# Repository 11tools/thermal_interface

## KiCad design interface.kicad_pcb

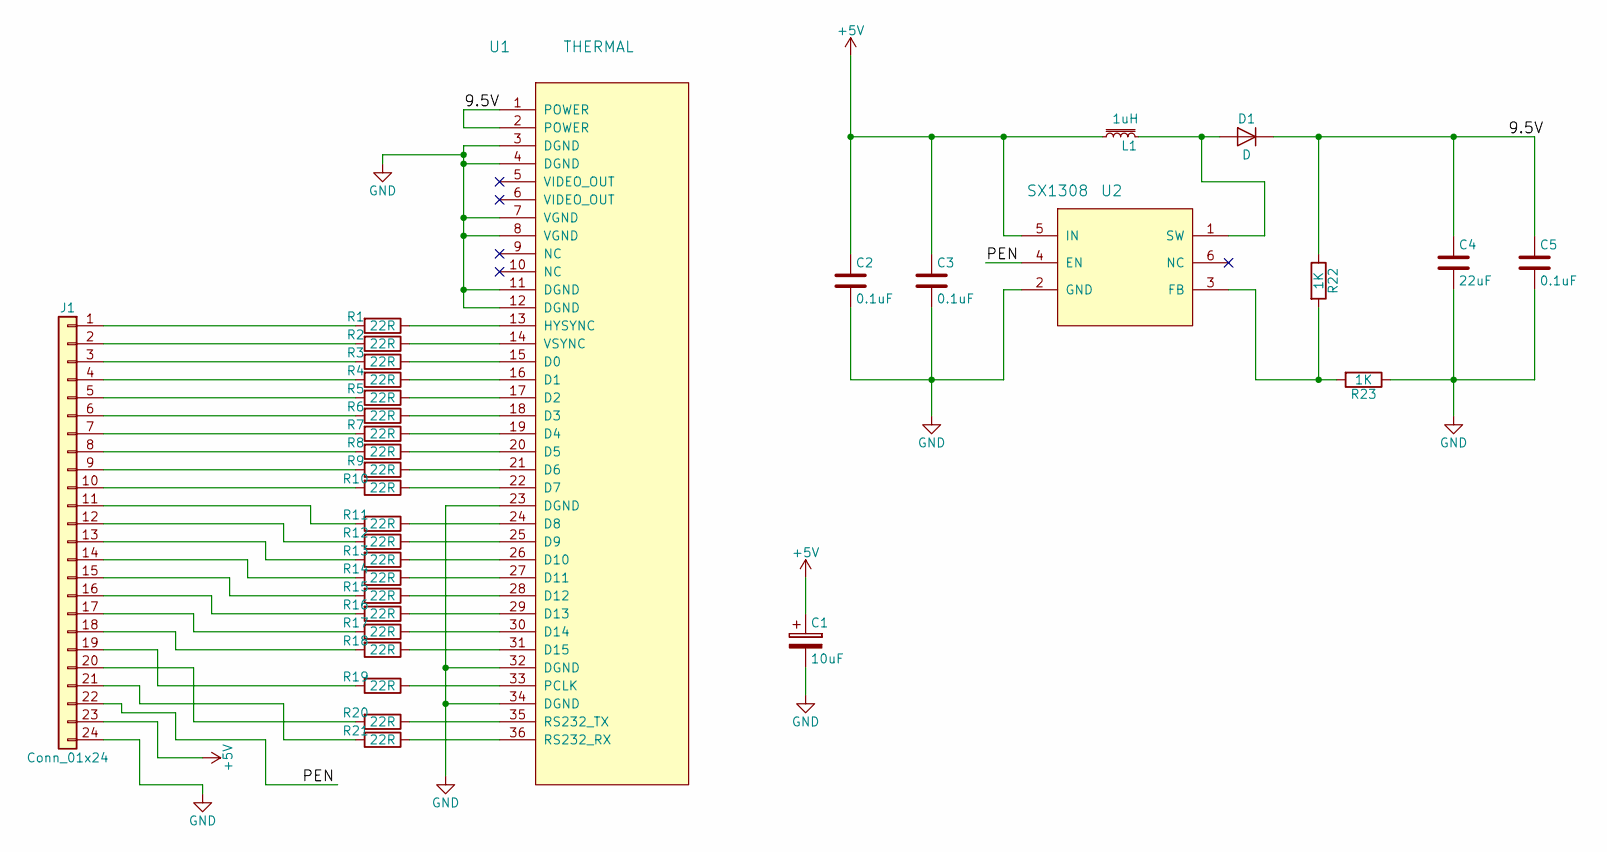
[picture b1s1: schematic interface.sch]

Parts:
C1: 10uF; C_1812
C2, C3, C5: 0.1uF; C_0603
C4: 22uF; C_0805
D1: D; D_SMA
J1: Conn_01x24; pin24
L1: 1uH; cd43
R1, R2, R3, R4, R5, R6, R7, R8, R9, R10, R11, R12, R13, R14, R15, R16, R17, R18, R19, R20, R21: 22R; R_0603
R22, R23: 1K; R_0603
U1: THERMAL; Hirose_FH12-36S-0.5SH_1x36-1MP_P0.50mm_Horizontal
U2: SX1308; SOT-23-6

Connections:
+5V: C1.1, C2.1, C3.1, J1.23, L1.2, U2.5 (IN)
/9.5V: C4.1, C5.1, D1.1 (K), R22.1, U1.1 (POWER), U1.2 (POWER)
/PEN: J1.22, U2.4 (EN)
GND: C1.2, C2.2, C3.2, C4.2, C5.2, J1.24, R23.1, U1.3 (DGND), U1.4 (DGND), U1.7 (VGND), U1.8 (VGND), U1.11 (DGND), U1.12 (DGND), U1.23 (DGND), U1.32 (DGND), U1.34 (DGND), U2.2 (GND)
unnamed: D1.2 (A), L1.1, U2.1 (SW)
unnamed: J1.1, R1.2
unnamed: J1.2, R2.2
unnamed: J1.3, R3.2
unnamed: J1.4, R4.2
unnamed: J1.5, R5.2
unnamed: J1.6, R6.2
unnamed: J1.7, R7.2
unnamed: J1.8, R8.2
unnamed: J1.9, R9.2
unnamed: J1.10, R10.2
unnamed: J1.11, R11.2
unnamed: J1.12, R12.2
unnamed: J1.13, R13.2
unnamed: J1.14, R14.2
unnamed: J1.15, R15.2
unnamed: J1.16, R16.2
unnamed: J1.17, R17.2
unnamed: J1.18, R18.2
unnamed: J1.19, R19.2
unnamed: J1.20, R20.2
unnamed: J1.21, R21.2
unnamed: R1.1, U1.13 (HYSYNC)
unnamed: R2.1, U1.14 (VSYNC)
unnamed: R3.1, U1.15 (D0)
unnamed: R4.1, U1.16 (D1)
unnamed: R5.1, U1.17 (D2)
unnamed: R6.1, U1.18 (D3)
unnamed: R7.1, U1.19 (D4)
unnamed: R8.1, U1.20 (D5)
unnamed: R9.1, U1.21 (D6)
unnamed: R10.1, U1.22 (D7)
unnamed: R11.1, U1.24 (D8)
unnamed: R12.1, U1.25 (D9)
unnamed: R13.1, U1.26 (D10)
unnamed: R14.1, U1.27 (D11)
unnamed: R15.1, U1.28 (D12)
unnamed: R16.1, U1.29 (D13)
unnamed: R17.1, U1.30 (D14)
unnamed: R18.1, U1.31 (D15)
unnamed: R19.1, U1.33 (PCLK)
unnamed: R20.1, U1.35 (RS232_TX)
unnamed: R21.1, U1.36 (RS232_RX)
unnamed: R22.2, R23.2, U2.3 (FB)

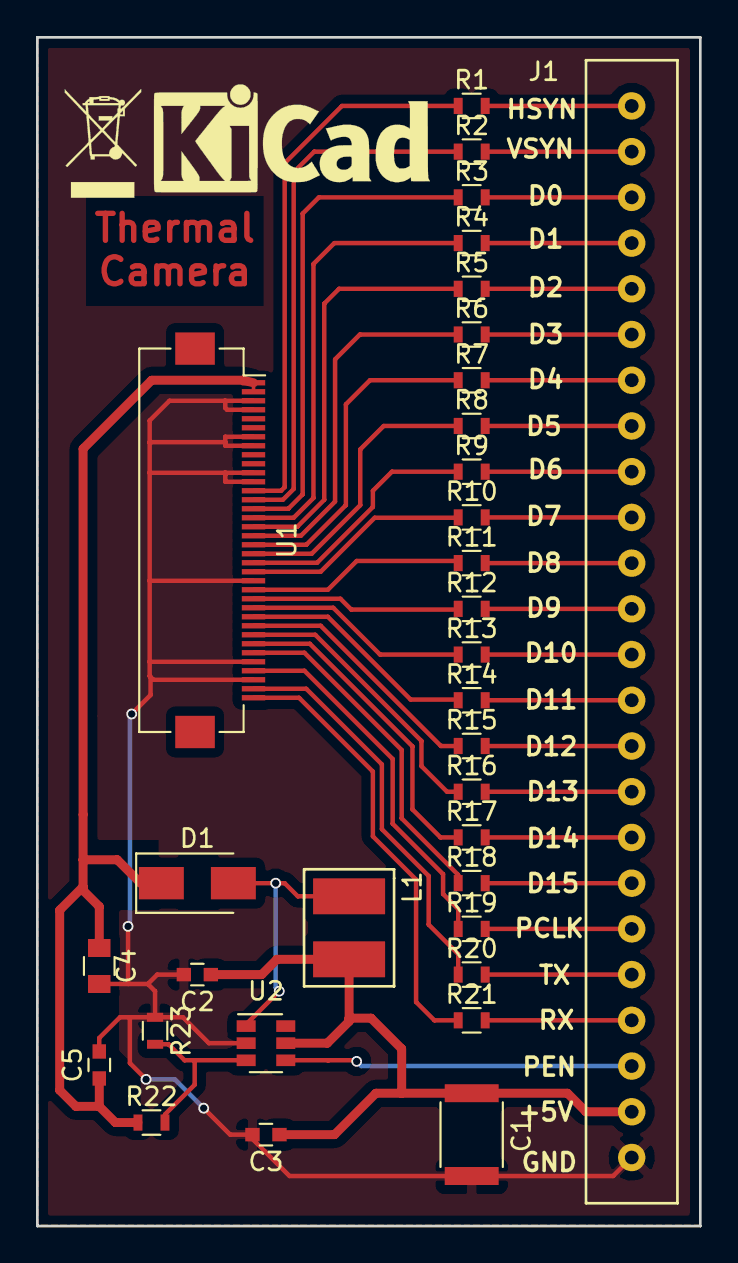
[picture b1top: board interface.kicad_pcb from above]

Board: 2 copper layers, 36.8 x 66.0 mm, 33 parts (0 on the bottom side), 48 nets.

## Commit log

2019-09-10 finish thermal camera interface
2019-09-10 add note
2019-09-10 finish pcb
2019-09-10 Revert "finish pcb"
    This reverts commit 664f2069ac5b8cd3e927f5ba02bd3a98c86c313e.
2019-09-10 finish and factory
